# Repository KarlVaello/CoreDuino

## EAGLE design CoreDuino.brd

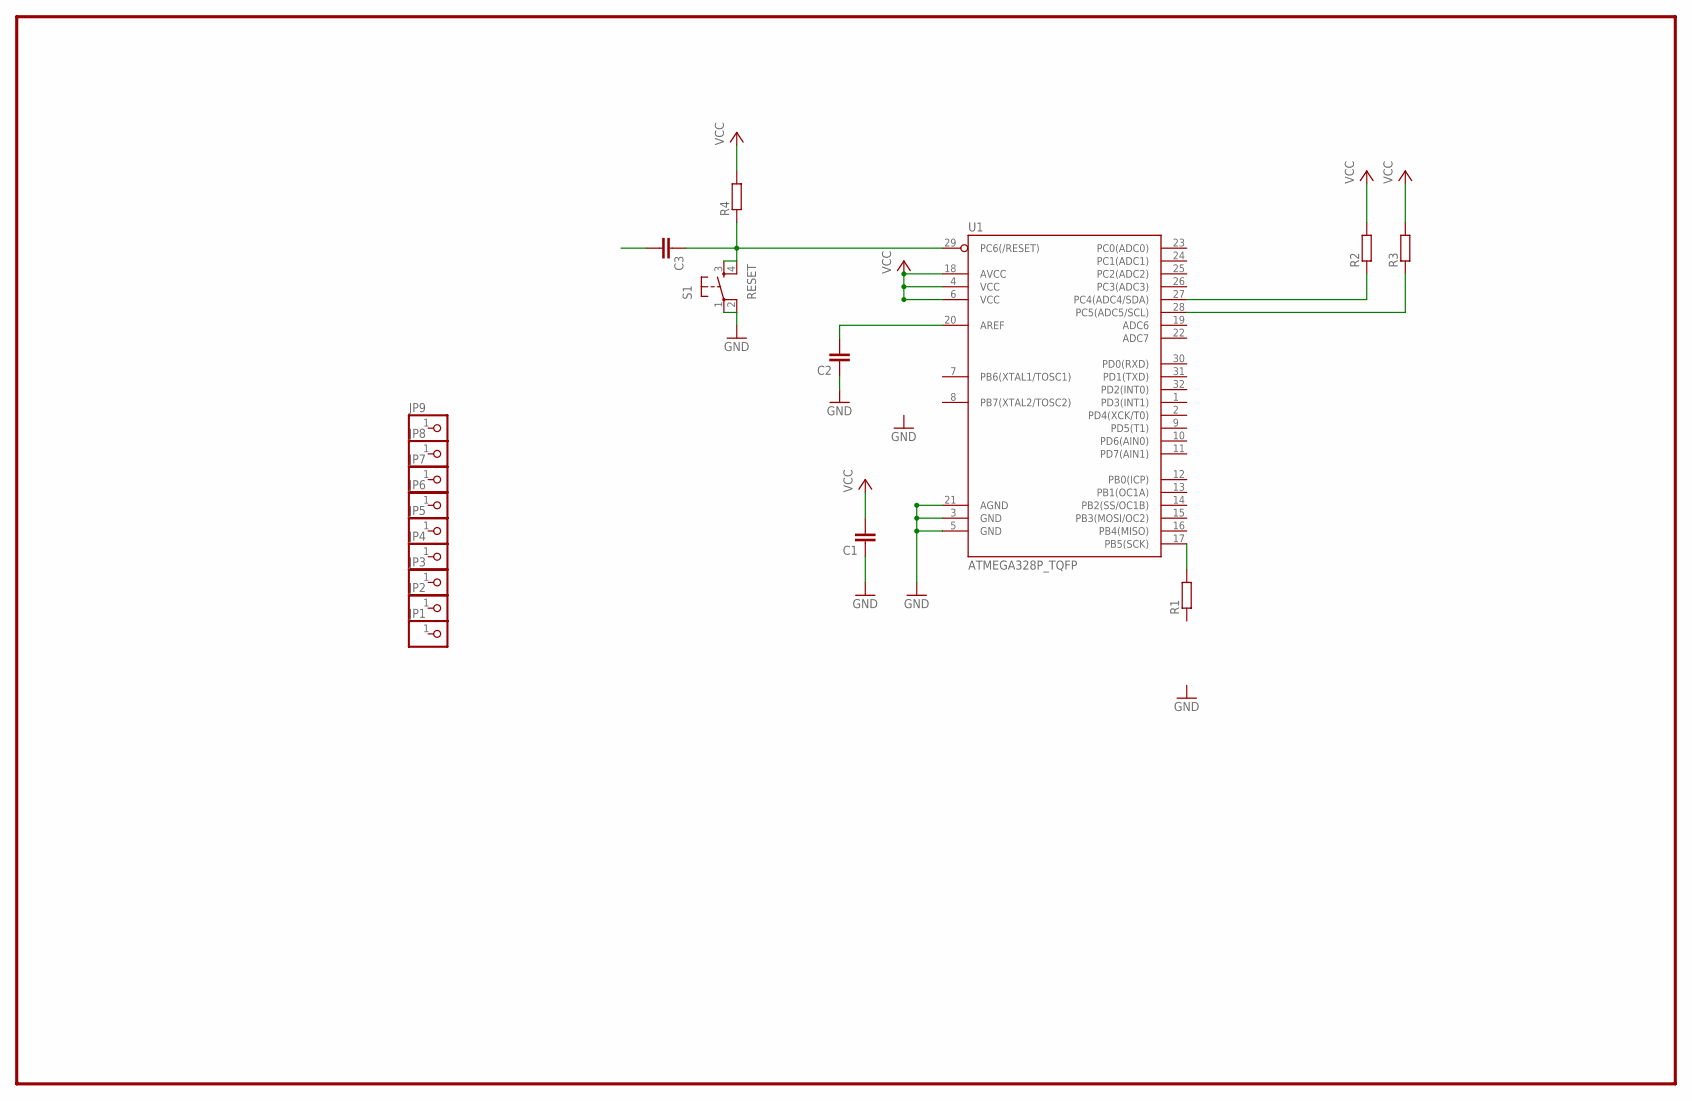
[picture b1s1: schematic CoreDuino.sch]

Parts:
C1, C2, C3: C-EUC0805; C0805
JP1, JP2, JP3, JP4, JP5, JP6, JP7, JP8, JP9: PINHD-1X1CB; 1X01-CLEANBIG
R1, R2, R3, R4: R-EU_R0805; R0805
S1: RESET; TACTILE-SWITCH-SMD
U1: ATMEGA328P_TQFP; TQFP32-08

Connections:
GND: C1.1, C2.1, S1.1, S1.2, U1.3 (GND), U1.5 (GND), U1.21 (AGND)
unnamed: C3.1, R4.1, S1.3, S1.4, U1.29 (PC6(/RESET))
unnamed: C2.2, U1.20 (AREF)
unnamed: R2.1, U1.27 (PC4(ADC4/SDA))
unnamed: R3.1, U1.28 (PC5(ADC5/SCL))
unnamed: R1.2, U1.17 (PB5(SCK))
VCC: C1.2, R2.2, R3.2, R4.2, U1.4 (VCC), U1.6 (VCC), U1.18 (AVCC)

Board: 2 copper layers, 18 parts (0 on the bottom side), 7 nets, no tracks yet.

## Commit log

2016-09-28 :circus_tent: Added .gitattributes & .gitignore files
2016-09-28 Initial Commit
    Initial Commit
2016-09-30 More Changes
    More Changes
2016-11-13 Added License file
    Added LICENSE.txt

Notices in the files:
parts and their libraries:
SparkFun-Retired: Licensing:Creative Commons ShareAlike 4.0 International - https://creativecommons.org/licenses/by-sa/4.0
